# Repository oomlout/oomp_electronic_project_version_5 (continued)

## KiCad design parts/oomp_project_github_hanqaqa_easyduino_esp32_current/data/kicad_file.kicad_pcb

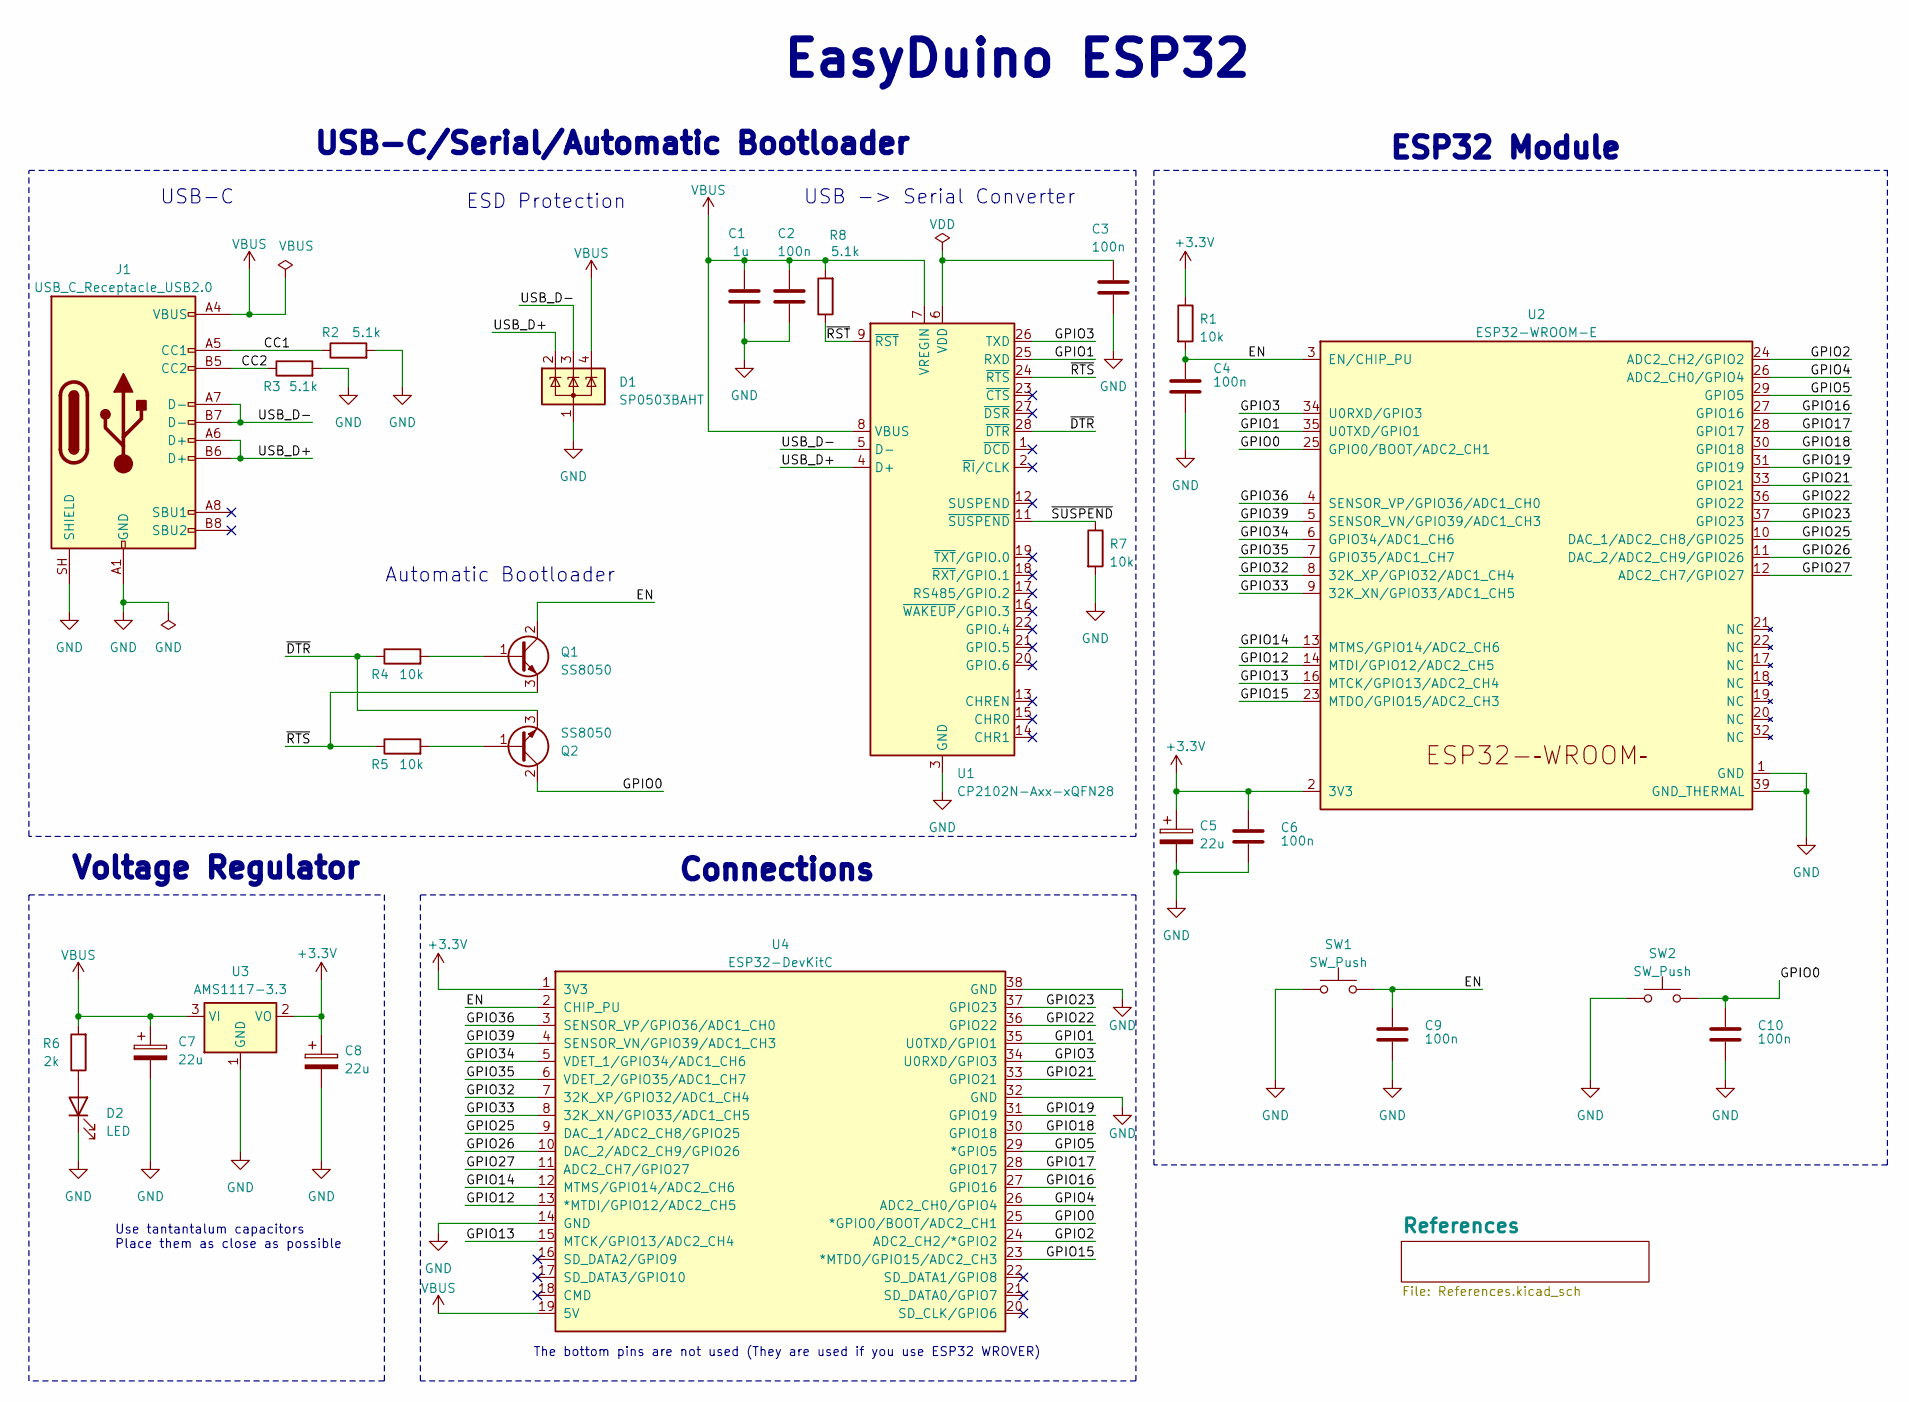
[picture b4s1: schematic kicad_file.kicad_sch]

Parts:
C1: 1u; C_0402_1005Metric; LCSC C52923
C2, C3, C4, C6, C9, C10: 100n; C_0402_1005Metric; LCSC C1525
C5, C7, C8: 22u; CP_EIA-3216-10_Kemet-I; LCSC C11366
D1: SP0503BAHT; SOT-143; LCSC C7074
D2: LED; LED_0402_1005Metric; LCSC C434447
J1: USB_C_Receptacle_USB2.0; USB_C_Receptacle_G-Switch_GT-USB-7010ASV; LCSC C2765186
Q1, Q2: SS8050; SOT-23W; LCSC C916392
R1, R4, R5, R7: 10k; R_0402_1005Metric; LCSC C25744
R2, R3, R8: 5.1k; R_0402_1005Metric; LCSC C25905
R6: 2k; R_0402_1005Metric; LCSC C4109
SW1, SW2: SW_Push; SW_Push_SPST_NO_Alps_SKRK; LCSC C720477
U1: CP2102N-Axx-xQFN28; QFN-28-1EP_5x5mm_P0.5mm_EP3.35x3.35mm; LCSC C6568
U2: ESP32-WROOM-E; ESP32-WROOM-32E; LCSC C701342
U3: AMS1117-3.3; SOT-223-3_TabPin2; LCSC C6186
U4: ESP32-DevKitC

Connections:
+3.3V: C5.1, C6.1, C8.1, R1.1, U2.2 (3V3), U3.2 (VO), U4.1 (3V3)
/CC1: J1.A5 (CC1), R2.1
/CC2: J1.B5 (CC2), R3.1
/EN: C4.1, C9.1, Q1.2 (C), R1.2, SW1.2, U2.3 (EN/CHIP_PU), U4.2 (CHIP_PU)
/GPIO0: C10.1, Q2.2 (C), SW2.2, U2.25 (GPIO0/BOOT/ADC2_CH1), U4.25 (*GPIO0/BOOT/ADC2_CH1)
/GPIO1: U1.25 (RXD), U2.35 (U0TXD/GPIO1), U4.35 (U0TXD/GPIO1)
/GPIO2: U2.24 (ADC2_CH2/GPIO2), U4.24 (ADC2_CH2/*GPIO2)
/GPIO3: U1.26 (TXD), U2.34 (U0RXD/GPIO3), U4.34 (U0RXD/GPIO3)
/GPIO4: U2.26 (ADC2_CH0/GPIO4), U4.26 (ADC2_CH0/GPIO4)
/GPIO5: U2.29 (GPIO5), U4.29 (*GPIO5)
/GPIO12: U2.14 (MTDI/GPIO12/ADC2_CH5), U4.13 (*MTDI/GPIO12/ADC2_CH5)
/GPIO13: U2.16 (MTCK/GPIO13/ADC2_CH4), U4.15 (MTCK/GPIO13/ADC2_CH4)
/GPIO14: U2.13 (MTMS/GPIO14/ADC2_CH6), U4.12 (MTMS/GPIO14/ADC2_CH6)
/GPIO15: U2.23 (MTDO/GPIO15/ADC2_CH3), U4.23 (*MTDO/GPIO15/ADC2_CH3)
/GPIO16: U2.27 (GPIO16), U4.27 (GPIO16)
/GPIO17: U2.28 (GPIO17), U4.28 (GPIO17)
/GPIO18: U2.30 (GPIO18), U4.30 (GPIO18)
/GPIO19: U2.31 (GPIO19), U4.31 (GPIO19)
/GPIO21: U2.33 (GPIO21), U4.33 (GPIO21)
/GPIO22: U2.36 (GPIO22), U4.36 (GPIO22)
/GPIO23: U2.37 (GPIO23), U4.37 (GPIO23)
/GPIO25: U2.10 (DAC_1/ADC2_CH8/GPIO25), U4.9 (DAC_1/ADC2_CH8/GPIO25)
/GPIO26: U2.11 (DAC_2/ADC2_CH9/GPIO26), U4.10 (DAC_2/ADC2_CH9/GPIO26)
/GPIO27: U2.12 (ADC2_CH7/GPIO27), U4.11 (ADC2_CH7/GPIO27)
/GPIO32: U2.8 (32K_XP/GPIO32/ADC1_CH4), U4.7 (32K_XP/GPIO32/ADC1_CH4)
/GPIO33: U2.9 (32K_XN/GPIO33/ADC1_CH5), U4.8 (32K_XN/GPIO33/ADC1_CH5)
/GPIO34: U2.6 (GPIO34/ADC1_CH6), U4.5 (VDET_1/GPIO34/ADC1_CH6)
/GPIO35: U2.7 (GPIO35/ADC1_CH7), U4.6 (VDET_2/GPIO35/ADC1_CH7)
/GPIO36: U2.4 (SENSOR_VP/GPIO36/ADC1_CH0), U4.3 (SENSOR_VP/GPIO36/ADC1_CH0)
/GPIO39: U2.5 (SENSOR_VN/GPIO39/ADC1_CH3), U4.4 (SENSOR_VN/GPIO39/ADC1_CH3)
/USB_D+: D1.2 (K), J1.A6 (D+), J1.B6 (D+), U1.4 (D+)
/USB_D-: D1.3 (K), J1.A7 (D-), J1.B7 (D-), U1.5 (D-)
/~DTR: Q2.3 (E), R4.1, U1.28 (~DTR)
/~RST: R8.1, U1.9 (~RST)
/~RTS: Q1.3 (E), R5.1, U1.24 (~RTS)
/~SUSPEND: R7.1, U1.11 (~SUSPEND)
GND: C1.2, C2.2, C3.2, C4.2, C5.2, C6.2, C7.2, C8.2, C9.2, C10.2, D1.1 (A), D2.1 (K), J1.A1 (GND), J1.A12 (GND), J1.B1 (GND), J1.B12 (GND), J1.SH (SHIELD), R2.2, R3.2, R7.2, SW1.1, SW2.1, U1.3 (GND), U1.29 (GND), U2.1 (GND), U2.15 (GND), U2.38 (GND), U2.39 (GND_THERMAL), U3.1 (GND), U4.14 (GND), U4.32 (GND), U4.38 (GND)
unnamed: D2.2 (A), R6.1
unnamed: Q1.1 (B), R4.2
unnamed: Q2.1 (B), R5.2
unnamed: C3.1, U1.6 (VDD)
VBUS: C1.1, C2.1, C7.1, D1.4 (K), J1.A4 (VBUS), J1.A9 (VBUS), J1.B4 (VBUS), J1.B9 (VBUS), R6.2, R8.2, U1.7 (VREGIN), U1.8 (VBUS), U3.3 (VI), U4.19 (5V)

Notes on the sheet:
ESD Protection
ESP32 Module
Voltage Regulator
Use tantantalum capacitors Place them as close as possible
Automatic Bootloader
USB-C
The bottom pins are not used (They are used if you use ESP32 WROVER)
USB -> Serial Converter
USB-C/Serial/Automatic Bootloader
EasyDuino ESP32
Connections

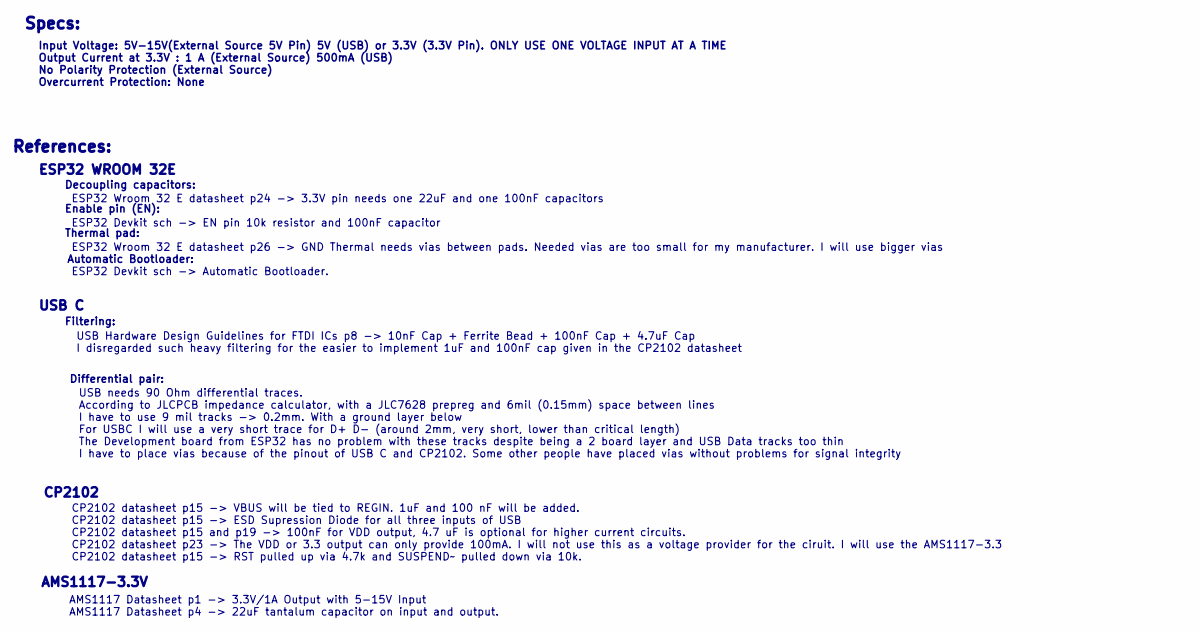
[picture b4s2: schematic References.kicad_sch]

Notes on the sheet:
ESP32 WROOM 32E
CP2102
AMS1117-3.3V
References:
Automatic Bootloader:
Decoupling capacitors:
ESP32 Wroom 32 E datasheet p24 -> 3.3V pin needs one 22uF and one 100nF capacitors ESP32 Devkit sch -> EN pin 10k resistor and 100nF capacitor ESP32 Wroom 32 E datasheet p26 -> GND Thermal needs vias between pads. Needed vias are too small for my manufacturer. I will use bigger vias ESP32 Devkit sc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
CP2102 datasheet p15 -> VBUS will be tied to REGIN. 1uF and 100 nF will be added. CP2102 datasheet p15 -> ESD Supression Diode for all three inputs of USB CP2102 datasheet p15 and p19 -> 100nF for VDD output, 4.7 uF is optional for higher current circuits. CP2102 datasheet p23 -> The VDD or 3.3 out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
Filtering:
Input Voltage: 5V-15V(External Source 5V Pin) 5V (USB) or 3.3V (3.3V Pin). ONLY USE ONE VOLTAGE INPUT AT A TIME Output Current at 3.3V : 1 A (External Source) 500mA (USB) No Polarity Protection (External Source) Overcurrent Protection: None
USB C
Specs:
Differential pair:
USB needs 90 Ohm differential traces. According to JLCPCB impedance calculator, with a JLC7628 prepreg and 6mil (0.15mm) space between lines I have to use 9 mil tracks -> 0.2mm. With a ground layer below For USBC I will use a very short trace for D+ D- (around 2mm, very short, lower than critical l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
USB Hardware Design Guidelines for FTDI ICs p8 -> 10nF Cap + Ferrite Bead + 100nF Cap + 4.7uF Cap I disregarded such heavy filtering for the easier to implement 1uF and 100nF cap given in the CP2102 datasheet
Enable pin (EN):
Thermal pad:
AMS1117 Datasheet p1 -> 3.3V/1A Output with 5-15V Input AMS1117 Datasheet p4 -> 22uF tantalum capacitor on input and output.

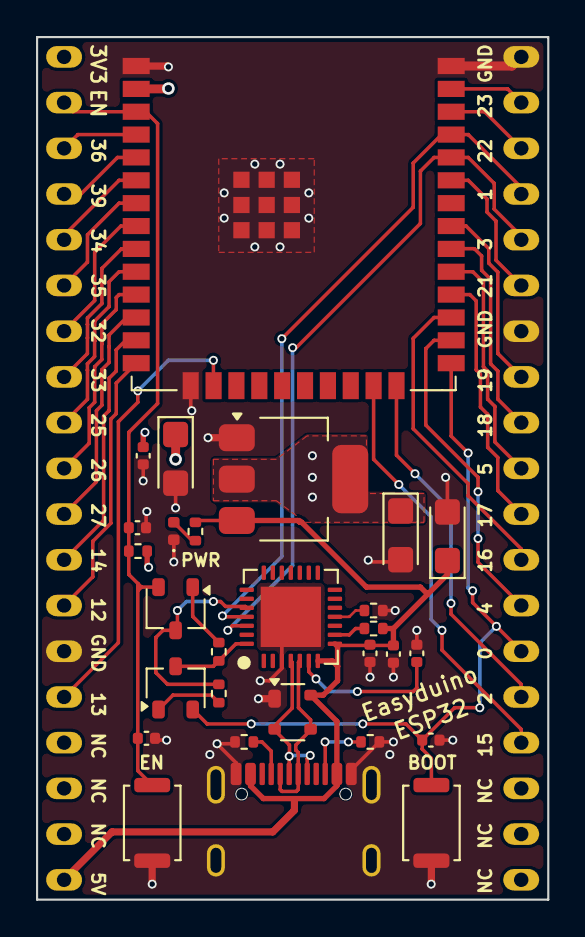
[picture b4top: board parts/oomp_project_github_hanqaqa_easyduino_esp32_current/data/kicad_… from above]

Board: 4 copper layers, 28.4 x 47.9 mm, 29 parts (0 on the bottom side), 42 nets.

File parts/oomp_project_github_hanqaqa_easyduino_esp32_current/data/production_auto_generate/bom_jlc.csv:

Comment,Designator,Footprint,LCSC Part #
100n,"C2,C3,C4,C6,C9,C10",Capacitor_SMD:C_0402_1005Metric,C1525
10k,"R1,R4,R5,R7",Resistor_SMD:R_0402_1005Metric,C25744
1u,C1,Capacitor_SMD:C_0402_1005Metric,C52923
22u,"C5,C7,C8",Capacitor_Tantalum_SMD:CP_EIA-3216-10_Kemet-I,C11366
2k,R6,Resistor_SMD:R_0402_1005Metric,C4109
5.1k,"R2,R3,R8",Resistor_SMD:R_0402_1005Metric,C25905
AMS1117-3.3,U3,Package_TO_SOT_SMD:SOT-223-3_TabPin2,C6186
CP2102N-Axx-xQFN28,U1,Package_DFN_QFN:QFN-28-1EP_5x5mm_P0.5mm_EP3.35x3.35mm,C6568
ESP32-DevKitC,U4,Espressif:ESP32-DevKitC,-
ESP32-WROOM-E,U2,Espressif:ESP32-WROOM-32E,C701342
LED,D2,LED_SMD:LED_0402_1005Metric,C434447
SP0503BAHT,D1,Package_TO_SOT_SMD:SOT-143,C7074
SS8050,"Q1,Q2",Package_TO_SOT_SMD:SOT-23W,C916392
SW_Push,"SW1,SW2",Button_Switch_SMD:SW_Push_SPST_NO_Alps_SKRK,C720477
USB_C_Receptacle_USB2.0,J1,Connector_USB:USB_C_Receptacle_G-Switch_GT-USB-7010ASV,C2765186

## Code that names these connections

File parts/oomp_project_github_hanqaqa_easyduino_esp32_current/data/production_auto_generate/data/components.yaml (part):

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  pads:
  - name: '1'
    type: smd
    net: /GPIO0
    x_mm: 153.0
    y_mm: 108.5
  - name: '2'
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    y_mm: 106.8
  - name: '2'
    type: smd
    net: /GPIO0
    x_mm: 140.25
    y_mm: 106.8
  - name: '3'
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    y_mm: 115.2
  - name: '2'
    type: smd
    net: /GPIO0
    x_mm: 153.51
    y_mm: 111.0
- reference: U1
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    y_mm: 101.15
  - name: '25'
    type: smd
    net: /GPIO1
    x_mm: 143.25
    y_mm: 101.65
  - name: '26'
    type: smd
    net: /GPIO3
    x_mm: 143.25
    y_mm: 102.15
  - name: '27'
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    y_mm: 73.59
  - name: '4'
    type: smd
    net: /GPIO36
    x_mm: 137.11
    y_mm: 74.86
  - name: '5'
    type: smd
    net: /GPIO39
    x_mm: 137.11
    y_mm: 76.13
  - name: '6'
    type: smd
    net: /GPIO34
    x_mm: 137.11
    y_mm: 77.4
  - name: '7'
    type: smd
    net: /GPIO35
    x_mm: 137.11
    y_mm: 78.67
  - name: '8'
    type: smd
    net: /GPIO32
    x_mm: 137.11
    y_mm: 79.94
  - name: '9'
    type: smd
    net: /GPIO33
    x_mm: 137.11
    y_mm: 81.21
  - name: '10'
    type: smd
    net: /GPIO25
    x_mm: 137.11
    y_mm: 82.48
  - name: '11'
    type: smd
    net: /GPIO26
    x_mm: 137.11
    y_mm: 83.75
  - name: '12'
    type: smd
    net: /GPIO27
    x_mm: 137.11
    y_mm: 85.02
  - name: '13'
    type: smd
    net: /GPIO14
    x_mm: 137.11
    y_mm: 86.29
  - name: '14'
    type: smd
    net: /GPIO12
    x_mm: 137.11
    y_mm: 87.56
  - name: '15'
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    y_mm: 88.81
  - name: '16'
    type: smd
    net: /GPIO13
    x_mm: 141.41
    y_mm: 88.81
  - name: '17'
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    y_mm: 88.81
  - name: '23'
    type: smd
    net: /GPIO15
    x_mm: 150.3
    y_mm: 88.81
  - name: '24'
    type: smd
    net: /GPIO2
    x_mm: 151.57
    y_mm: 88.81
  - name: '25'
    type: smd
    net: /GPIO0
    x_mm: 154.61
    y_mm: 87.56
  - name: '26'
    type: smd
    net: /GPIO4
    x_mm: 154.61
    y_mm: 86.29
  - name: '27'
    type: smd
    net: /GPIO16
    x_mm: 154.61
    y_mm: 85.02
  - name: '28'
    type: smd
    net: /GPIO17
    x_mm: 154.61
    y_mm: 83.75
  - name: '29'
    type: smd
    net: /GPIO5
    x_mm: 154.61
    y_mm: 82.48
  - name: '30'
    type: smd
    net: /GPIO18
    x_mm: 154.61
    y_mm: 81.21
  - name: '31'
    type: smd
    net: /GPIO19
    x_mm: 154.61
    y_mm: 79.94
  - name: '32'
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    y_mm: 78.67
  - name: '33'
    type: smd
    net: /GPIO21
    x_mm: 154.61
    y_mm: 77.4
  - name: '34'
    type: smd
    net: /GPIO3
    x_mm: 154.61
    y_mm: 76.13
  - name: '35'
    type: smd
    net: /GPIO1
    x_mm: 154.61
    y_mm: 74.86
  - name: '36'
    type: smd
    net: /GPIO22
    x_mm: 154.61
    y_mm: 73.59
  - name: '37'
    type: smd
    net: /GPIO23
    x_mm: 154.61
    y_mm: 72.32
  - name: '38'
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    y_mm: 73.08272
  - name: '3'
    type: thru_hole
    net: /GPIO36
    x_mm: 133.10368
    y_mm: 75.62272
  - name: '4'
    type: thru_hole
    net: /GPIO39
    x_mm: 133.10368
    y_mm: 78.16272
  - name: '5'
    type: thru_hole
    net: /GPIO34
    x_mm: 133.10368
    y_mm: 80.70272
  - name: '6'
    type: thru_hole
    net: /GPIO35
    x_mm: 133.10368
    y_mm: 83.24272
  - name: '7'
    type: thru_hole
    net: /GPIO32
    x_mm: 133.10368
    y_mm: 85.78272
  - name: '8'
    type: thru_hole
    net: /GPIO33
    x_mm: 133.10368
    y_mm: 88.32272
  - name: '9'
    type: thru_hole
    net: /GPIO25
    x_mm: 133.10368
    y_mm: 90.86272
  - name: '10'
    type: thru_hole
    net: /GPIO26
    x_mm: 133.10368
    y_mm: 93.40272
  - name: '11'
    type: thru_hole
    net: /GPIO27
    x_mm: 133.10368
    y_mm: 95.94272
  - name: '12'
    type: thru_hole
    net: /GPIO14
    x_mm: 133.10368
    y_mm: 98.48272
  - name: '13'
    type: thru_hole
    net: /GPIO12
    x_mm: 133.10368
    y_mm: 101.02272
  - name: '14'
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    y_mm: 103.56272
  - name: '15'
    type: thru_hole
    net: /GPIO13
    x_mm: 133.10368
    y_mm: 106.10272
  - name: '16'
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    y_mm: 111.18272
  - name: '23'
    type: thru_hole
    net: /GPIO15
    x_mm: 158.50368
    y_mm: 108.64272
  - name: '24'
    type: thru_hole
    net: /GPIO2
    x_mm: 158.50368
    y_mm: 106.10272
  - name: '25'
    type: thru_hole
    net: /GPIO0
    x_mm: 158.50368
    y_mm: 103.56272
  - name: '26'
    type: thru_hole
    net: /GPIO4
    x_mm: 158.50368
    y_mm: 101.02272
  - name: '27'
    type: thru_hole
    net: /GPIO16
    x_mm: 158.50368
    y_mm: 98.48272
  - name: '28'
    type: thru_hole
    net: /GPIO17
    x_mm: 158.50368
    y_mm: 95.94272
  - name: '29'
    type: thru_hole
    net: /GPIO5
    x_mm: 158.50368
    y_mm: 93.40272
  - name: '30'
    type: thru_hole
    net: /GPIO18
    x_mm: 158.50368
    y_mm: 90.86272
  - name: '31'
    type: thru_hole
    net: /GPIO19
    x_mm: 158.50368
    y_mm: 88.32272
  - name: '32'
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    y_mm: 85.78272
  - name: '33'
    type: thru_hole
    net: /GPIO21
    x_mm: 158.50368
    y_mm: 83.24272
  - name: '34'
    type: thru_hole
    net: /GPIO3
    x_mm: 158.50368
    y_mm: 80.70272
  - name: '35'
    type: thru_hole
    net: /GPIO1
    x_mm: 158.50368
    y_mm: 78.16272
  - name: '36'
    type: thru_hole
    net: /GPIO22
    x_mm: 158.50368
    y_mm: 75.62272
  - name: '37'
    type: thru_hole
    net: /GPIO23
    x_mm: 158.50368
    y_mm: 73.08272
  - name: '38'
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
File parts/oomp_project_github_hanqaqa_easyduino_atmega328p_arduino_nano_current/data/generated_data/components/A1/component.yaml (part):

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      position:
        x: 127.0
        y: 149.86
      net: PD1
      net_aliases:
      - PD1
      net_scope: sheet
      no_connect: false
      connected_to:
      - reference: U1
        pin_number: '31'
        pin_name: PD1
      - reference: U3
        pin_number: '25'
        pin_name: RXD
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      position:
        x: 127.0
        y: 147.32
      net: PD0
      net_aliases:
      - PD0
      net_scope: sheet
      no_connect: false
      connected_to:
      - reference: U1
        pin_number: '30'
        pin_name: PD0
      - reference: U3
        pin_number: '26'
        pin_name: TXD
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      position:
        x: 152.4
        y: 149.86
      net: PC6
      net_aliases:
      - PC6
      net_scope: sheet
      no_connect: false
      connected_to:
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        pin_name: ''
      - reference: U1
        pin_number: '29'
        pin_name: ~{RESET}/PC6
    - number: '4'
      name: GND
      electrical_type: power_in
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      position:
        x: 127.0
        y: 152.4
      net: PD2
      net_aliases:
      - PD2
      net_scope: sheet
      no_connect: false
      connected_to:
      - reference: U1
        pin_number: '32'
        pin_name: PD2
    - number: '6'
      name: D3
      electrical_type: bidirectional
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      position:
        x: 127.0
        y: 154.94
      net: PD3
      net_aliases:
      - PD3
      net_scope: sheet
      no_connect: false
      connected_to:
      - reference: U1
        pin_number: '1'
        pin_name: PD3
    - number: '7'
      name: D4
      electrical_type: bidirectional
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      position:
        x: 127.0
        y: 157.48
      net: PD4
      net_aliases:
      - PD4
      net_scope: sheet
      no_connect: false
      connected_to:
      - reference: U1
        pin_number: '2'
        pin_name: PD4
    - number: '8'
      name: D5
      electrical_type: bidirectional
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      position:
        x: 127.0
        y: 160.02
      net: PD5
      net_aliases:
      - PD5
      net_scope: sheet
      no_connect: false
      connected_to:
      - reference: U1
        pin_number: '9'
        pin_name: PD5
    - number: '9'
      name: D6
      electrical_type: bidirectional
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      position:
        x: 127.0
        y: 162.56
      net: PD6
      net_aliases:
      - PD6
      net_scope: sheet
      no_connect: false
      connected_to:
      - reference: U1
        pin_number: '10'
        pin_name: PD6
    - number: '10'
      name: D7
      electrical_type: bidirectional
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      position:
        x: 127.0
        y: 165.1
      net: PD7
      net_aliases:
      - PD7
      net_scope: sheet
      no_connect: false
      connected_to:
      - reference: U1
        pin_number: '11'
        pin_name: PD7
    - number: '11'
      name: D8
      electrical_type: bidirectional
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      position:
        x: 127.0
        y: 167.64
      net: PB0
      net_aliases:
      - PB0
      net_scope: sheet
      no_connect: false
      connected_to:
      - reference: U1
        pin_number: '12'
        pin_name: PB0
    - number: '12'
      name: D9
      electrical_type: bidirectional
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      position:
        x: 127.0
        y: 170.18
      net: PB1
      net_aliases:
      - PB1
      net_scope: sheet
      no_connect: false
      connected_to:
      - reference: U1
        pin_number: '13'
        pin_name: PB1
    - number: '13'
      name: D10
      electrical_type: bidirectional
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      position:
        x: 127.0
        y: 172.72
      net: PB2
      net_aliases:
      - PB2
      net_scope: sheet
      no_connect: false
      connected_to:
      - reference: U1
        pin_number: '14'
        pin_name: PB2
    - number: '14'
      name: D11
      electrical_type: bidirectional
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      position:
        x: 127.0
        y: 175.26
      net: PB3
      net_aliases:
      - PB3
      net_scope: sheet
      no_connect: false
      connected_to:
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        pin_name: Pin_4
      - reference: U1
        pin_number: '15'
        pin_name: PB3
    - number: '15'
      name: D12
      electrical_type: bidirectional
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      position:
        x: 127.0
        y: 177.8
      net: PB4
      net_aliases:
      - PB4
      net_scope: sheet
      no_connect: false
      connected_to:
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        pin_name: Pin_1
      - reference: U1
        pin_number: '16'
        pin_name: PB4
    - number: '16'
      name: D13
      electrical_type: bidirectional
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      position:
        x: 127.0
        y: 180.34
      net: PB5
      net_aliases:
      - PB5
      net_scope: sheet
      no_connect: false
      connected_to:
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        pin_name: ''
      - reference: U1
        pin_number: '17'
        pin_name: PB5
    - number: '17'
      name: 3V3
      electrical_type: power_out
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      position:
        x: 152.4
        y: 162.56
      net: PC0
      net_aliases:
      - PC0
      net_scope: sheet
      no_connect: false
      connected_to:
      - reference: U1
        pin_number: '23'
        pin_name: PC0
    - number: '20'
      name: A1
      electrical_type: bidirectional
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      position:
        x: 152.4
        y: 165.1
      net: PC1
      net_aliases:
      - PC1
      net_scope: sheet
      no_connect: false
      connected_to:
      - reference: U1
        pin_number: '24'
        pin_name: PC1
    - number: '21'
      name: A2
      electrical_type: bidirectional
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      position:
        x: 152.4
        y: 167.64
      net: PC2
      net_aliases:
      - PC2
      net_scope: sheet
      no_connect: false
      connected_to:
      - reference: U1
        pin_number: '25'
        pin_name: PC2
    - number: '22'
      name: A3
      electrical_type: bidirectional
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      position:
        x: 152.4
        y: 170.18
      net: PC3
      net_aliases:
      - PC3
      net_scope: sheet
      no_connect: false
      connected_to:
      - reference: U1
        pin_number: '26'
        pin_name: PC3
    - number: '23'
      name: A4
      electrical_type: bidirectional
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      position:
        x: 152.4
        y: 172.72
      net: PC4
      net_aliases:
      - PC4
      net_scope: sheet
      no_connect: false
      connected_to:
      - reference: U1
        pin_number: '27'
        pin_name: PC4
    - number: '24'
      name: A5
      electrical_type: bidirectional
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      position:
        x: 152.4
        y: 175.26
      net: PC5
      net_aliases:
      - PC5
      net_scope: sheet
      no_connect: false
      connected_to:
      - reference: U1
        pin_number: '28'
        pin_name: PC5
    - number: '25'
      name: A6
      electrical_type: bidirectional
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        pin_name: VCC
      - reference: U1
        pin_number: '18'
        pin_name: AVCC
      - reference: U2
        pin_number: '2'
        pin_name: VO
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      position:
        x: 152.4
        y: 147.32
      net: PC6
      net_aliases:
      - PC6
      net_scope: sheet
      no_connect: false
      connected_to:
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        pin_name: ''
      - reference: U1
        pin_number: '29'
        pin_name: ~{RESET}/PC6
    - number: '29'
      name: GND
      electrical_type: power_in
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    pin_name: '1'
  - reference: U1
    pin_number: '1'
    pin_name: PD3
  - reference: U1
    pin_number: '10'
    pin_name: PD6
  - reference: U1
    pin_number: '11'
    pin_name: PD7
  - reference: U1
    pin_number: '12'
    pin_name: PB0
  - reference: U1
    pin_number: '13'
    pin_name: PB1
  - reference: U1
    pin_number: '14'
    pin_name: PB2
  - reference: U1
    pin_number: '15'
    pin_name: PB3
  - reference: U1
    pin_number: '16'
    pin_name: PB4
  - reference: U1
    pin_number: '17'
    pin_name: PB5
  - reference: U1
    pin_number: '18'
    pin_name: AVCC
  - reference: U1
    pin_number: '19'
    pin_name: ADC6
  - reference: U1
    pin_number: '2'
    pin_name: PD4
  - reference: U1
    pin_number: '20'
    pin_name: AREF
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    pin_name: ADC7
  - reference: U1
    pin_number: '23'
    pin_name: PC0
  - reference: U1
    pin_number: '24'
    pin_name: PC1
  - reference: U1
    pin_number: '25'
    pin_name: PC2
  - reference: U1
    pin_number: '26'
    pin_name: PC3
  - reference: U1
    pin_number: '27'
    pin_name: PC4
  - reference: U1
    pin_number: '28'
    pin_name: PC5
  - reference: U1
    pin_number: '29'
    pin_name: ~{RESET}/PC6
  - reference: U1
    pin_number: '3'
    pin_name: GND
  - reference: U1
    pin_number: '30'
    pin_name: PD0
  - reference: U1
    pin_number: '31'
    pin_name: PD1
  - reference: U1
    pin_number: '32'
    pin_name: PD2
  - reference: U1
    pin_number: '4'
    pin_name: VCC
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    pin_name: VCC
  - reference: U1
    pin_number: '9'
    pin_name: PD5
  - reference: U2
    pin_number: '1'
    pin_name: GND
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    layers:
    - '*.Cu'
    - '*.Mask'
    net: /PD1
    net_number: null
    pin_function: D1/TX_1
    pin_type: bidirectional
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    layers:
    - '*.Cu'
    - '*.Mask'
    net: /PD0
    net_number: null
    pin_function: D0/RX_2
    pin_type: bidirectional
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    layers:
    - '*.Cu'
    - '*.Mask'
    net: /PC6
    net_number: null
    pin_function: ~{RESET}_3
    pin_type: input
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    layers:
    - '*.Cu'
    - '*.Mask'
    net: /PD2
    net_number: null
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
